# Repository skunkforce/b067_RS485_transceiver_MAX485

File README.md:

# edgy_board number b067
This design is part of the [edgy board project](https://github.com/skunkforce/edgy_boards). It provides the RS485 transceiver functionality of the chip MAX485 via interfaces osf.010 uart. 

# getting started
This repository uses submodules. After cloning use the command 

```$ git submodule update --init --recursive```

to pull the submodules before opening the project with kicad. 

# Tests
Tests can be found in [TESTS.md](TESTS.md)

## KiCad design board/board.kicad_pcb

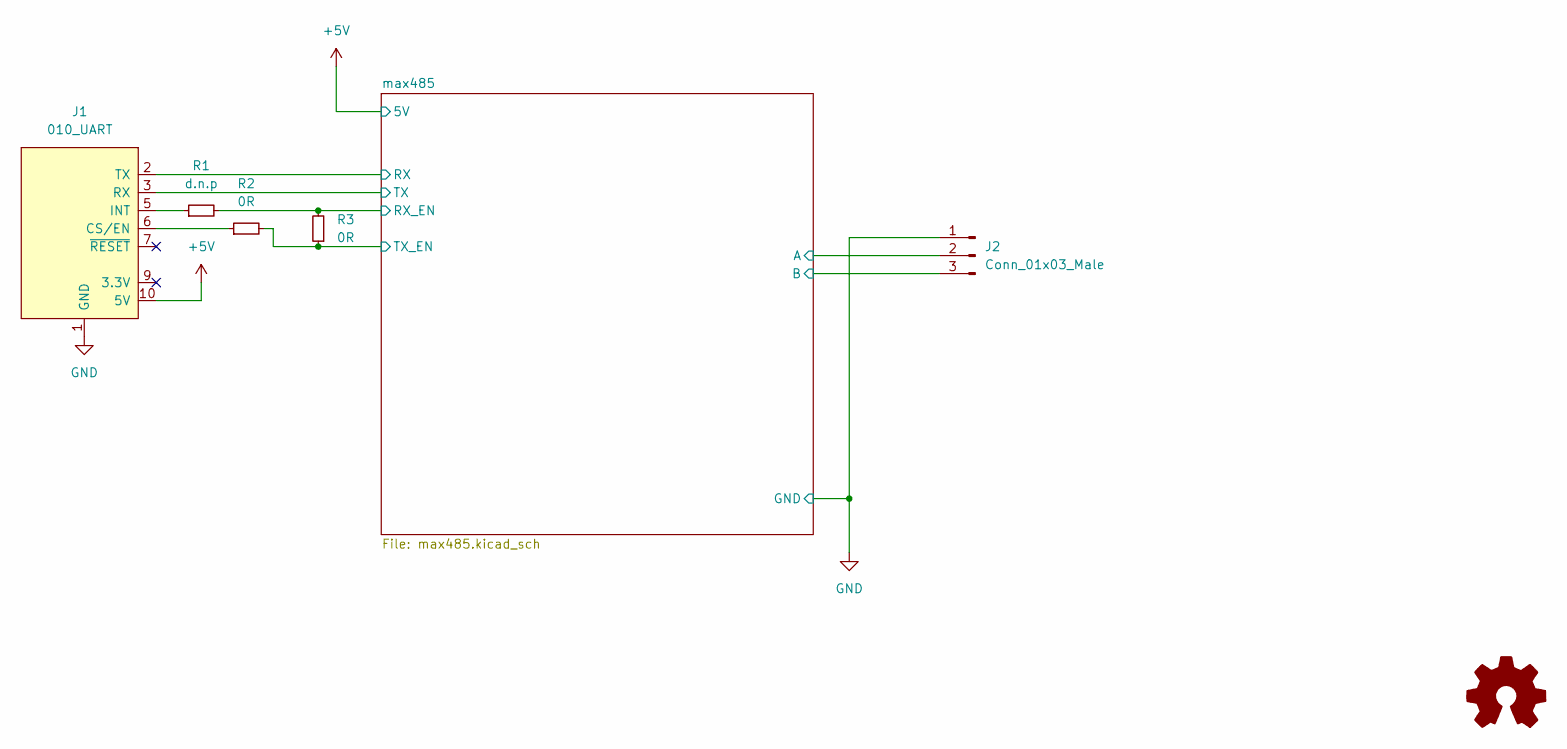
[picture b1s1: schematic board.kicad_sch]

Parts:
J1: 010_UART; on_edge_2x05_device
J2: Conn_01x03_Male; PinHeader_1x03_P2.54mm_Vertical
LOGO1: Logo_Open_Hardware_Small; OSHW-Symbol_6.7x6mm_SilkScreen
R1: d.n.p; R_0603_1608Metric
R2, R3: 0R; R_0603_1608Metric

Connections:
+5V: J1.10 (5V); also elsewhere on the board
/max485/A: J2.2; also elsewhere on the board
/max485/B: J2.3; also elsewhere on the board
/max485/RX: J1.2 (TX); also elsewhere on the board
/max485/RX_EN: R1.2, R3.2; also elsewhere on the board
/max485/TX: J1.3 (RX); also elsewhere on the board
/max485/TX_EN: R2.2, R3.1; also elsewhere on the board
GND: J1.1 (GND), J2.1; also elsewhere on the board
unnamed: J1.5 (INT), R1.1
unnamed: J1.6 (CS/EN), R2.1

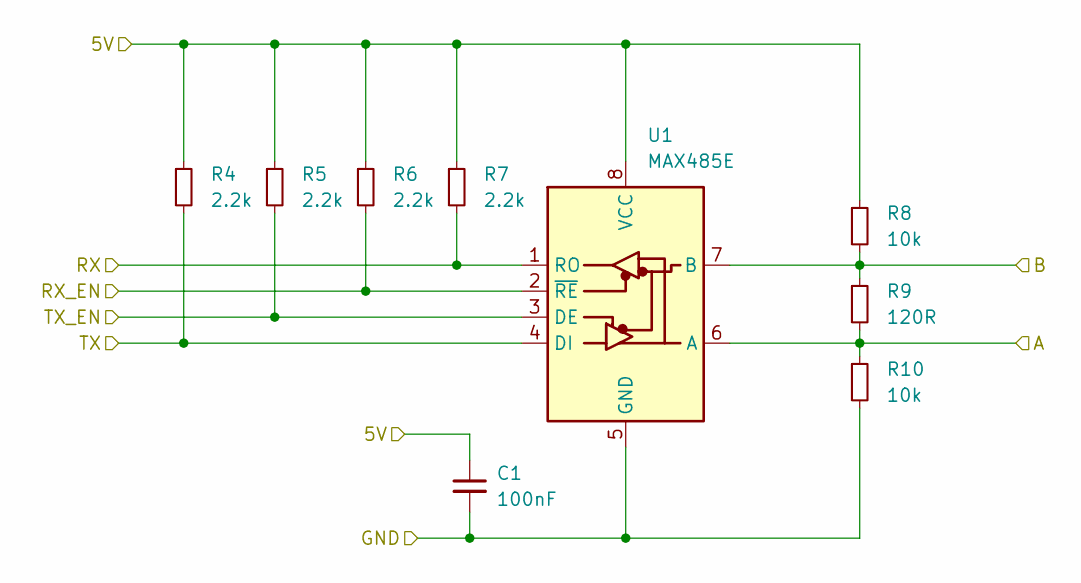
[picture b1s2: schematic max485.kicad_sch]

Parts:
C1: 100nF; C_0603_1608Metric
R4, R5, R6, R7: 2.2k; R_0603_1608Metric
R8, R10: 10k; R_0603_1608Metric
R9: 120R; R_0603_1608Metric
U1: MAX485E; SO-8_3.9x4.9mm_P1.27mm

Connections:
+5V: C1.1, R4.1, R5.1, R6.1, R7.1, R8.1, U1.8 (VCC); also elsewhere on the board
/max485/A: R9.2, R10.1, U1.6 (A); also elsewhere on the board
/max485/B: R8.2, R9.1, U1.7 (B); also elsewhere on the board
/max485/RX: R7.2, U1.1 (RO); also elsewhere on the board
/max485/RX_EN: R6.2, U1.2 (~RE); also elsewhere on the board
/max485/TX: R4.2, U1.4 (DI); also elsewhere on the board
/max485/TX_EN: R5.2, U1.3 (DE); also elsewhere on the board
GND: C1.2, R10.2, U1.5 (GND); also elsewhere on the board

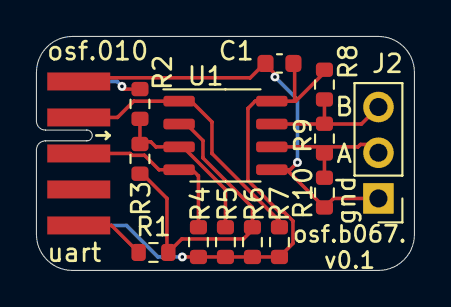
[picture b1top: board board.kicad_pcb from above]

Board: 2 copper layers, 21.0 x 13.0 mm, 15 parts (1 on the bottom side), 10 nets.

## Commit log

2023-02-17 initial
2023-02-18 changed implementation.kicad_sch to max485.kicad_sch in order to avoid clashing on the name implementation with other edgies in a composition
2023-02-18 changed supply to 5V and fixed up silkscreen
2023-02-18 added test description and readme contents
